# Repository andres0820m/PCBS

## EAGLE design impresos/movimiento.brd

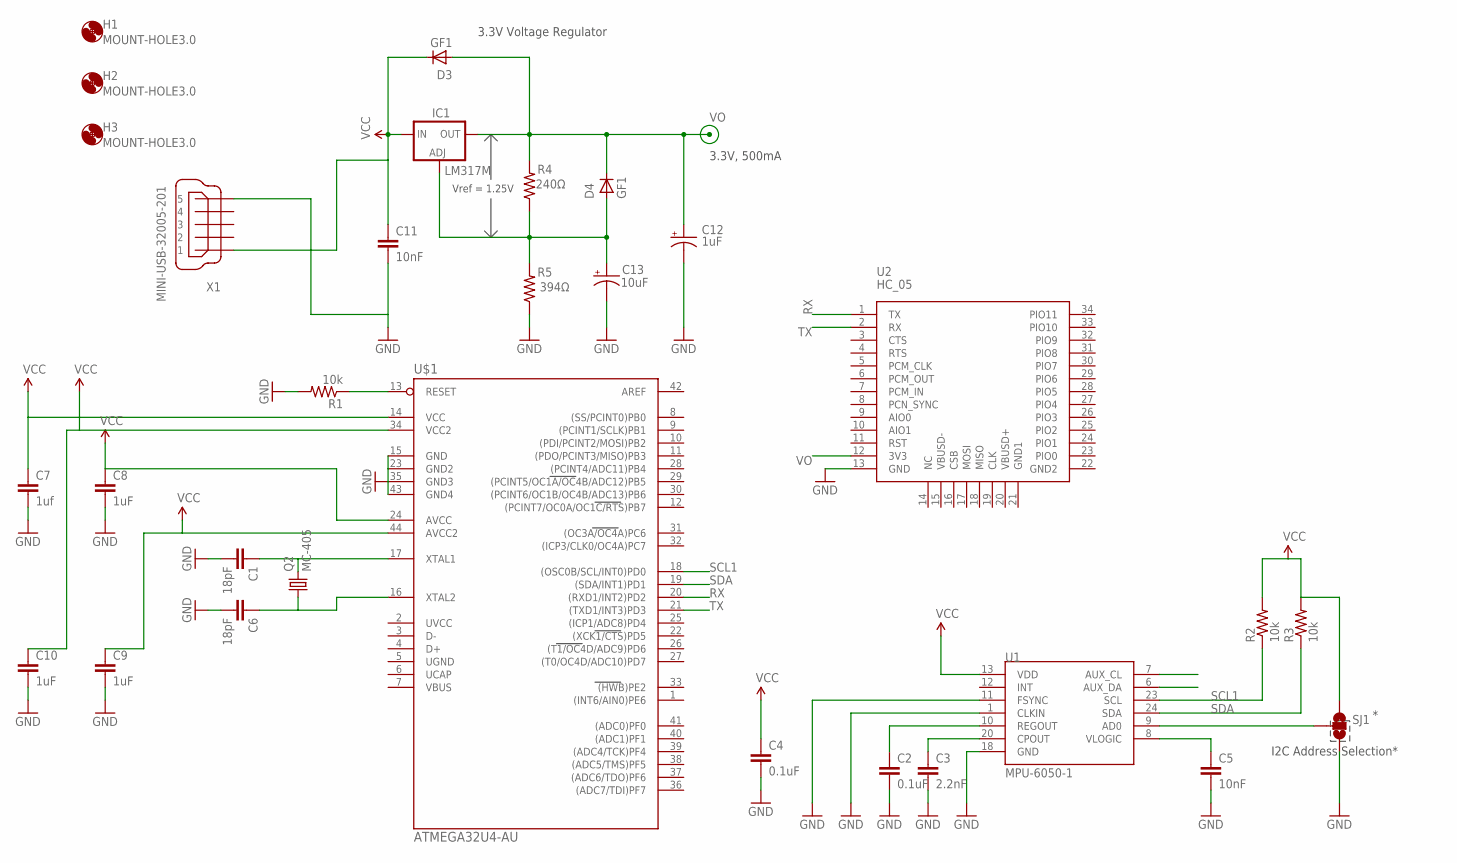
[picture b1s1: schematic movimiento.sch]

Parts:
C1, C6: 18pF; 0603-CAP
C2, C4: 0.1uF; 0603-CAP
C3: 2.2nF; 0603-CAP
C5, C11: 10nF; 0603-CAP
C7: 1uf; 0603-CAP
C8, C9, C10: 1uF; 0603-CAP
C12: 1uF; 085CS_1AR
C13: 10uF; 085CS_1AR
D3, D4: GF1; SMA-DO214AC
H1, H2, H3: MOUNT-HOLE3.0; 3,0
IC1: LM317MBSTT3; SOT223; PARTNUMBER LM317M
Q2: MC-405
R1, R2, R3: 10k; 0603-RES
R4: 240Ω; M0805
R5: 394Ω; M0805
SJ1: SOLDERJUMPER_2WAYPASTE2&3; SJ_3_PASTE2&3
U1: MPU-6050-1; QFN-24-4MM2
U2: HC_05; BLUETOOTH_SMD
U$1: ATMEGA32U4-AU; TQFP44
X1: MINI-USB-32005-201; 32005-201

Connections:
ADO: SJ1.2, U1.9 (AD0)
AUX_SCL: U1.7 (AUX_CL)
AUX_SDA: U1.6 (AUX_DA)
GND: C1.2, C2.2, C3.2, C4.2, C5.2, C6.2, C7.2, C8.2, C9.2, C10.2, C11.2, C12.-, C13.-, R1.2, R5.1, SJ1.3, U1.1 (CLKIN), U1.11 (FSYNC), U1.18 (GND), U2.13 (GND), X1.5
unnamed: C1.1, Q2.2, U$1.17 (XTAL1)
unnamed: C6.1, Q2.1, U$1.16 (XTAL2)
unnamed: R1.1, U$1.13 (RESET)
unnamed: U$1.15 (GND), U$1.23 (GND2), U$1.35 (GND3), U$1.43 (GND4)
unnamed: C3.1, U1.20 (CPOUT)
unnamed: C2.1, U1.10 (REGOUT)
unnamed: C13.+, D4.A, IC1.1 (ADJ), R4.1, R5.2
RX: U2.1 (TX), U$1.20 ((RXD1/INT2)PD2)
SCL1: R2.1, U1.23 (SCL), U$1.18 ((OSC0B/SCL/INT0)PD0)
SDA: R3.1, U1.24 (SDA), U$1.19 ((SDA/INT1)PD1)
TX: U2.2 (RX), U$1.21 ((TXD1/INT3)PD3)
VCC: C4.1, C7.1, C8.1, C9.1, C10.1, R2.2, R3.2, SJ1.1, U1.13 (VDD), U$1.14 (VCC), U$1.24 (AVCC), U$1.34 (VCC2), U$1.44 (AVCC2)
VIN: C11.1, D3.K (C), IC1.3 (IN), X1.1
VIO: C5.1, U1.8 (VLOGIC)
VO: C12.+, D3.A, D4.K (C), IC1.4 (OUT), R4.2, U2.12 (3V3)

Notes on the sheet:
I2C Address Selection*
3.3V Voltage Regulator
Vref = 1.25V
3.3V, 500mA

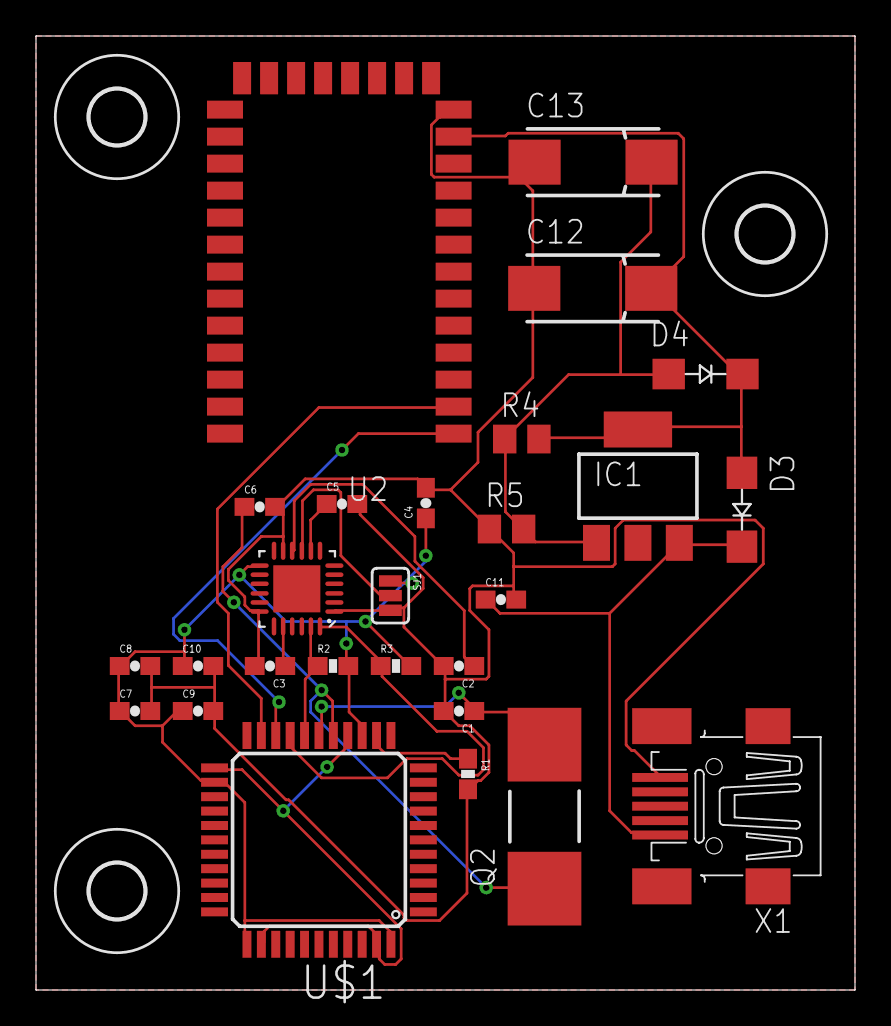
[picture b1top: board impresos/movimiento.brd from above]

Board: 2 copper layers, 45.5 x 53.0 mm, 30 parts (0 on the bottom side), 17 nets.

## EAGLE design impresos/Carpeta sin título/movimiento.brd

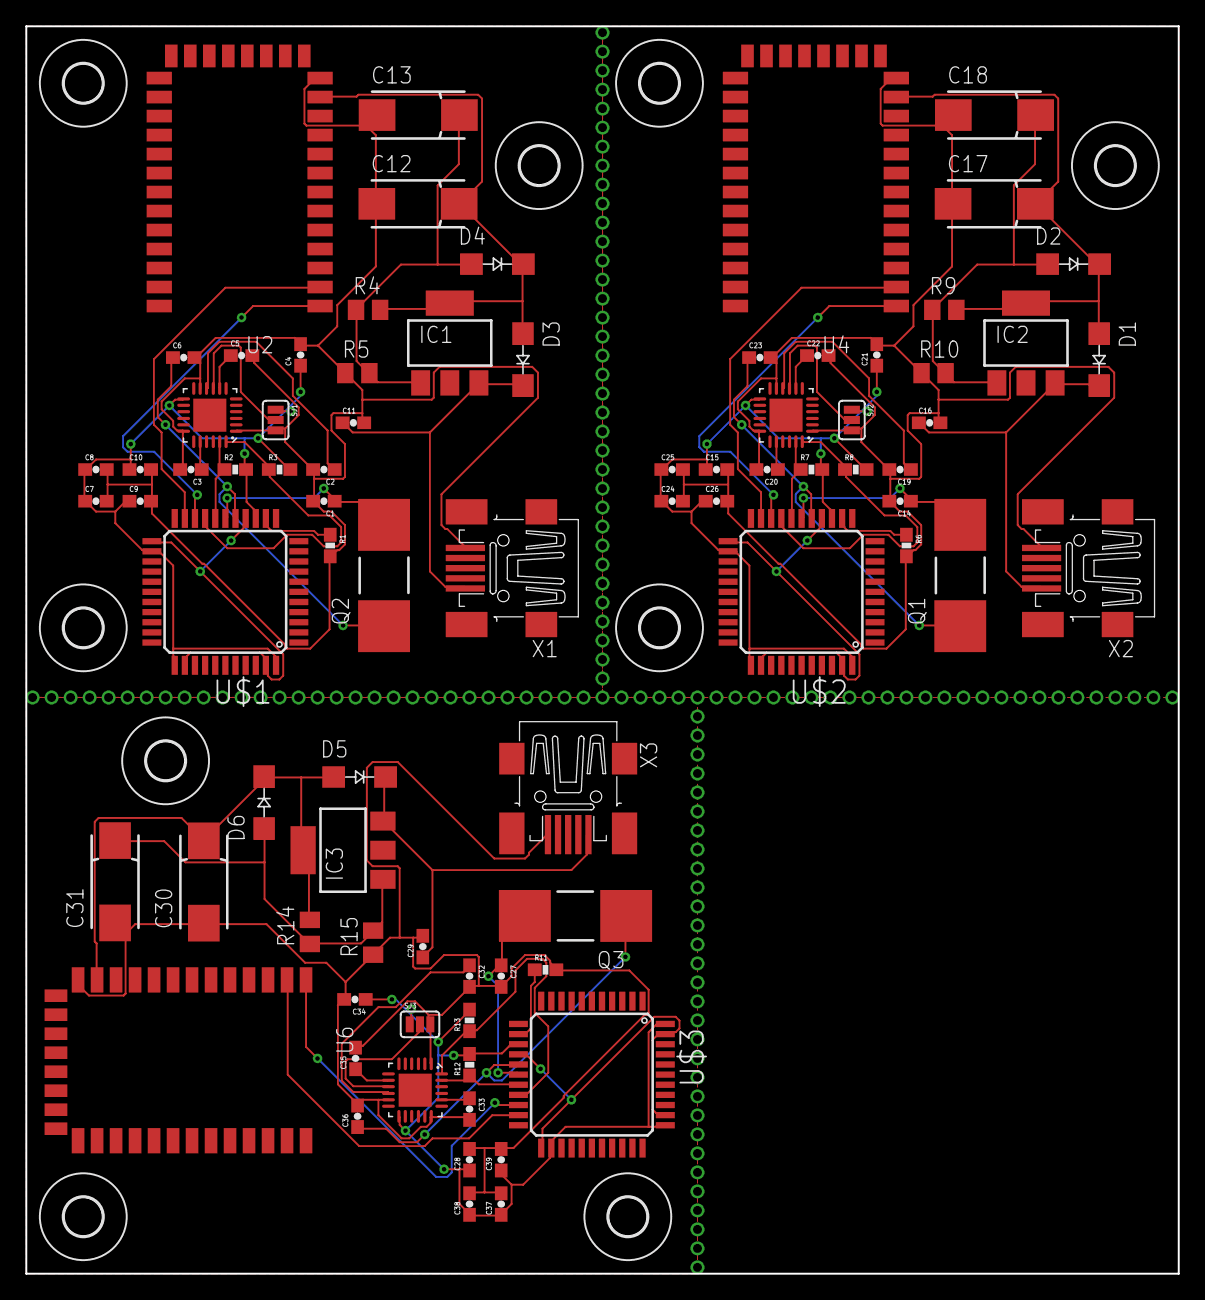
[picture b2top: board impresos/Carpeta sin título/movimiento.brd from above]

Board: 2 copper layers, 91.0 x 98.5 mm, 90 parts (0 on the bottom side), 51 nets.

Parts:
C1, C2, C4, C6, C14, C19, C21, C23, C27, C32, C34, C36: 0.1uF; 0603-CAP
C3, C20, C33: 2.2nF; 0603-CAP
C5, C7, C8, C9, C10, C11, C15, C16, C22, C24, C25, C26, C28, C29, C35, C37, C38, C39: 10nF; 0603-CAP
C12, C17, C30: 1uF; 085CS_1AR
C13, C18, C31: 10uF; 085CS_1AR
D1, D2, D3, D4, D5, D6: GF1; SMA-DO214AC
H1, H2, H3, H4, H5, H6, H7, H8, H9: MOUNT-HOLE3.0; 3,0
IC1, IC2, IC3: LM317MBSTT3; SOT223
Q1, Q2, Q3: MC-405
R1, R2, R3, R6, R7, R8, R11, R12, R13: 10k; 0603-RES
R4, R9, R14: 240Ω; M0805
R5, R10, R15: 394Ω; M0805
SJ1, SJ2, SJ3: SJ_3_PASTE2&3
U1, U3, U5: MPU-6050-1; QFN-24-4MM2
U2, U4, U6: HC_05; BLUETOOTH_SMD
U$1, U$2, U$3: ATMEGA32U4-AU; TQFP44
X1, X2, X3: MINI-USB-32005-201; 32005-201

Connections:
ADO: SJ1.2, U1.9
ADO1: SJ2.2, U3.9
ADO2: SJ3.2, U5.9
GND: C1.2, C2.2, C3.2, C4.2, C5.2, C6.2, C7.2, C8.2, C9.2, C10.2, C11.2, C12.-, C13.-, R1.2, R5.1, SJ1.3, U1.1, U1.11, U1.18, U2.13, X1.5
GND1: C14.2, C15.2, C16.2, C17.-, C18.-, C19.2, C20.2, C21.2, C22.2, C23.2, C24.2, C25.2, C26.2, R6.2, R10.1, SJ2.3, U3.1, U3.11, U3.18, U4.13, X2.5
GND2: C27.2, C28.2, C29.2, C30.-, C31.-, C32.2, C33.2, C34.2, C35.2, C36.2, C37.2, C38.2, C39.2, R11.2, R15.1, SJ3.3, U5.1, U5.11, U5.18, U6.13, X3.5
unnamed: C1.1, Q2.2, U$1.17
unnamed: C6.1, Q2.1, U$1.16
unnamed: R1.1, U$1.13
unnamed: U$1.15, U$1.23, U$1.35, U$1.43
unnamed: C3.1, U1.20
unnamed: C2.1, U1.10
unnamed: C13.+, D4.A, IC1.1, R4.1, R5.2
unnamed: C14.1, Q1.2, U$2.17
unnamed: C23.1, Q1.1, U$2.16
unnamed: C20.1, U3.20
unnamed: C19.1, U3.10
unnamed: R6.1, U$2.13
unnamed: U$2.15, U$2.23, U$2.35, U$2.43
unnamed: C18.+, D2.A, IC2.1, R9.1, R10.2
unnamed: C27.1, Q3.2, U$3.17
unnamed: C36.1, Q3.1, U$3.16
unnamed: C33.1, U5.20
unnamed: C32.1, U5.10
unnamed: R11.1, U$3.13
unnamed: U$3.15, U$3.23, U$3.35, U$3.43
unnamed: C31.+, D6.A, IC3.1, R14.1, R15.2
RX: U2.1, U$1.20
RX1: U4.1, U$2.20
RX2: U6.1, U$3.20
SCL1: R2.1, U1.23, U$1.18
SCL2: R7.1, U3.23, U$2.18
SCL3: R12.1, U5.23, U$3.18
SDA: R3.1, U1.24, U$1.19
SDA1: R8.1, U3.24, U$2.19
SDA2: R13.1, U5.24, U$3.19
TX: U2.2, U$1.21
TX1: U4.2, U$2.21
TX2: U6.2, U$3.21
VCC: C4.1, C7.1, C8.1, C9.1, C10.1, R2.2, R3.2, SJ1.1, U1.13, U$1.14, U$1.24, U$1.34, U$1.44
VCC1: C15.1, C21.1, C24.1, C25.1, C26.1, R7.2, R8.2, SJ2.1, U3.13, U$2.14, U$2.24, U$2.34, U$2.44
VCC2: C28.1, C34.1, C37.1, C38.1, C39.1, R12.2, R13.2, SJ3.1, U5.13, U$3.14, U$3.24, U$3.34, U$3.44
VIN: C11.1, D3.K, IC1.3, X1.1
VIN1: C16.1, D1.K, IC2.3, X2.1
VIN2: C29.1, D5.K, IC3.3, X3.1
VIO: C5.1, U1.8
VIO1: C22.1, U3.8
VIO2: C35.1, U5.8
VO: C12.+, D3.A, D4.K, IC1.4, R4.2, U2.12
VO1: C17.+, D1.A, D2.K, IC2.4, R9.2, U4.12
VO2: C30.+, D5.A, D6.K, IC3.4, R14.2, U6.12
